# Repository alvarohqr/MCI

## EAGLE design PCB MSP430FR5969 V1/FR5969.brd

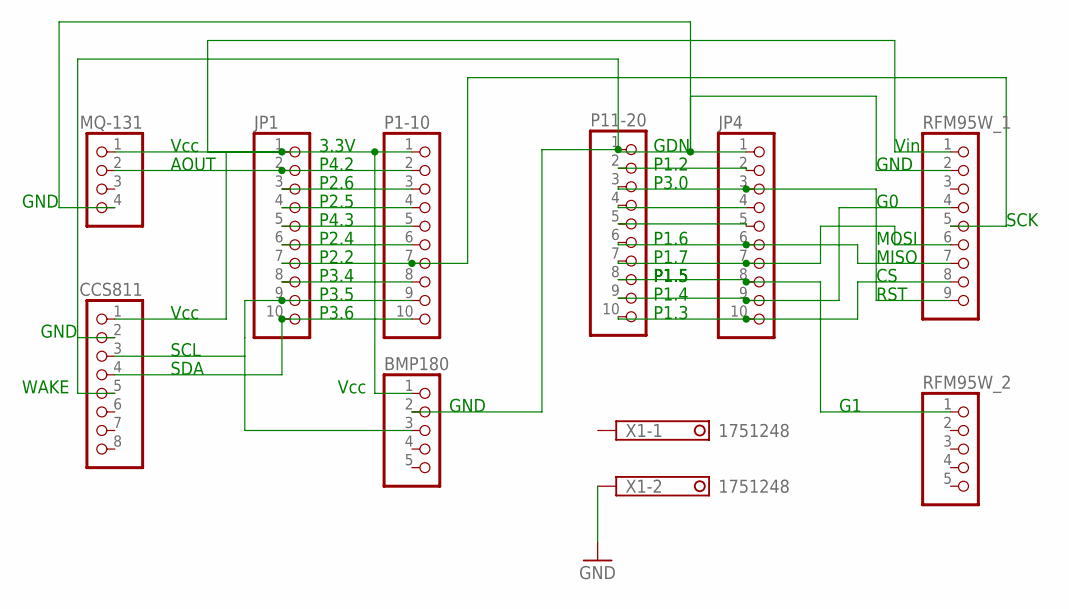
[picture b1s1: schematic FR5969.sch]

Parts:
BMP180: PINHD-1X5; 1X05
CCS811: PINHD-1X8; 1X08
JP1, JP4: PINHD-1X10; 1X10
MQ-131: PINHD-1X4; 1X04
P1-10, P11-20: PINHD-1X10; 1X10
RFM95W_1: PINHD-1X9; 1X09
RFM95W_2: PINHD-1X5; 1X05
X1: 1751248

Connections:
GND: X1.2
unnamed: BMP180.1, CCS811.1, JP1.1, MQ-131.1, P1-10.1, RFM95W_1.1
unnamed: JP1.2, MQ-131.2, P1-10.2
unnamed: JP1.3, P1-10.3
unnamed: JP1.4, P1-10.4
unnamed: JP1.5, P1-10.5
unnamed: JP1.6, P1-10.6
unnamed: JP1.7, P1-10.7, RFM95W_1.5
unnamed: JP1.8, P1-10.8
unnamed: BMP180.3, CCS811.3, JP1.9, P1-10.9
unnamed: CCS811.4, JP1.10, P1-10.10
unnamed: JP4.10, P11-20.10, RFM95W_1.8
unnamed: JP4.9, P11-20.9, RFM95W_1.4
unnamed: JP4.8, P11-20.8, RFM95W_2.1
unnamed: JP4.7, P11-20.7, RFM95W_1.6
unnamed: JP4.6, P11-20.6, RFM95W_1.7
unnamed: JP4.5, P11-20.5
unnamed: JP4.4, P11-20.4
unnamed: JP4.3, P11-20.3, RFM95W_1.9
unnamed: JP4.2, P11-20.2
unnamed: BMP180.2, CCS811.2, CCS811.5, JP4.1, MQ-131.4, P11-20.1, RFM95W_1.2

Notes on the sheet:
3.3V
P4.2
P2.6
P2.5
P4.3
P2.2
P2.4
P3.4
P3.5
P3.6
GDN
P1.2
P3.0
P1.6
P1.7
P1.5
P1.4
P1.3
MOSI
MISO
SCK
RST
Vin
GND
Vcc
AOUT
SCL
SDA
WAKE

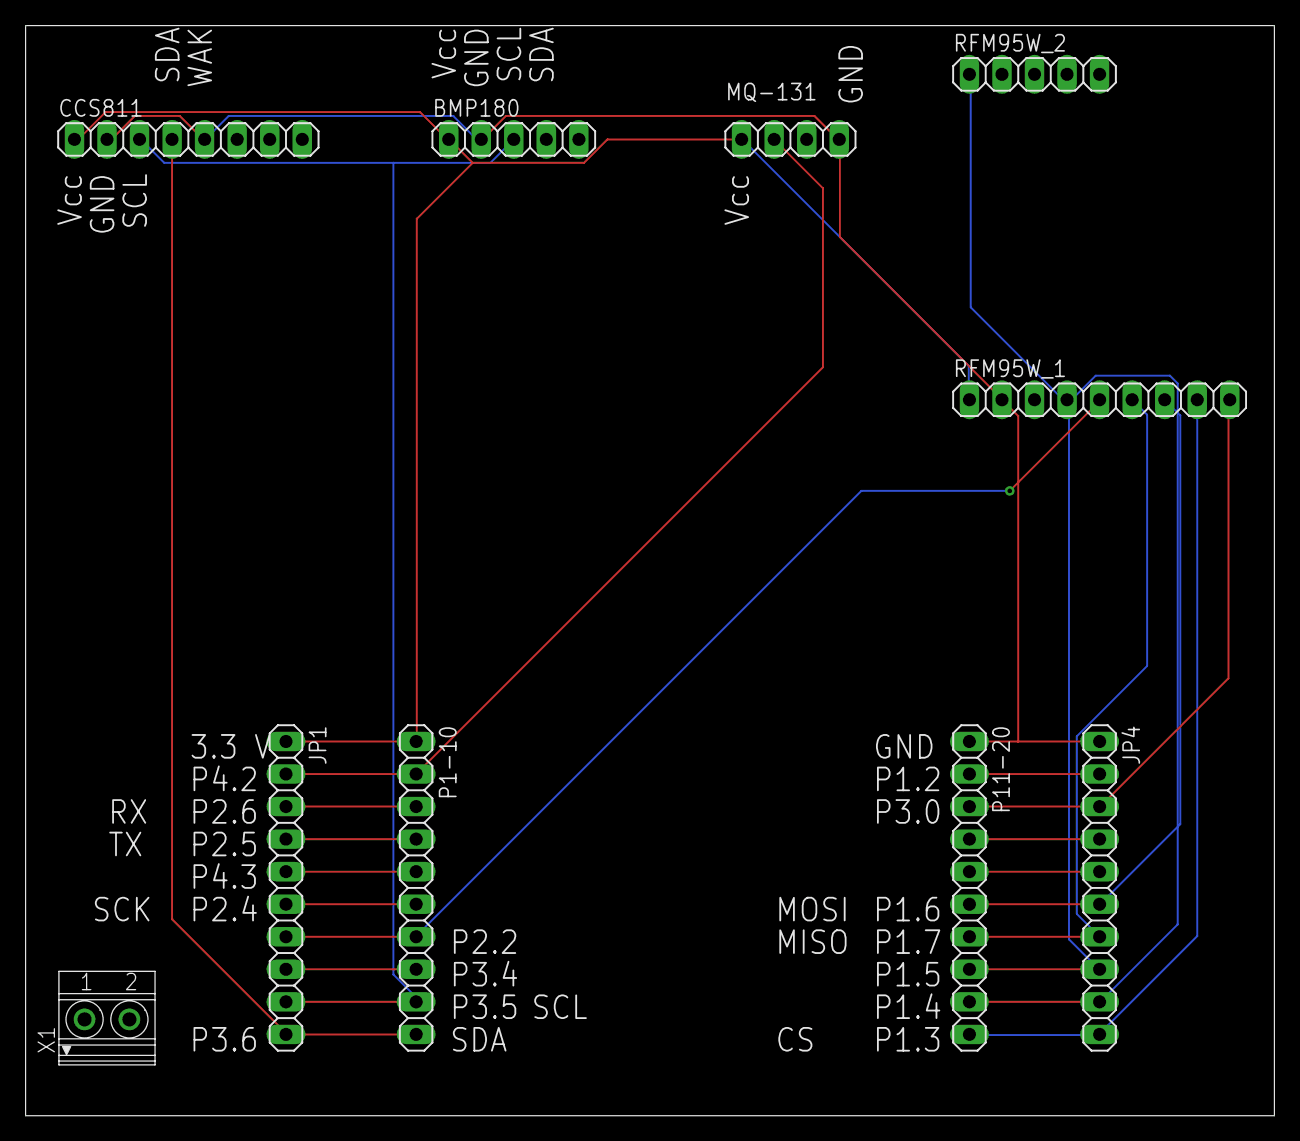
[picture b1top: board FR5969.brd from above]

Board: 2 copper layers, 97.5 x 85.1 mm, 10 parts (0 on the bottom side), 20 nets.

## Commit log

2022-03-31 Add files via upload
    Sensor de eCO2 y TVOC's
